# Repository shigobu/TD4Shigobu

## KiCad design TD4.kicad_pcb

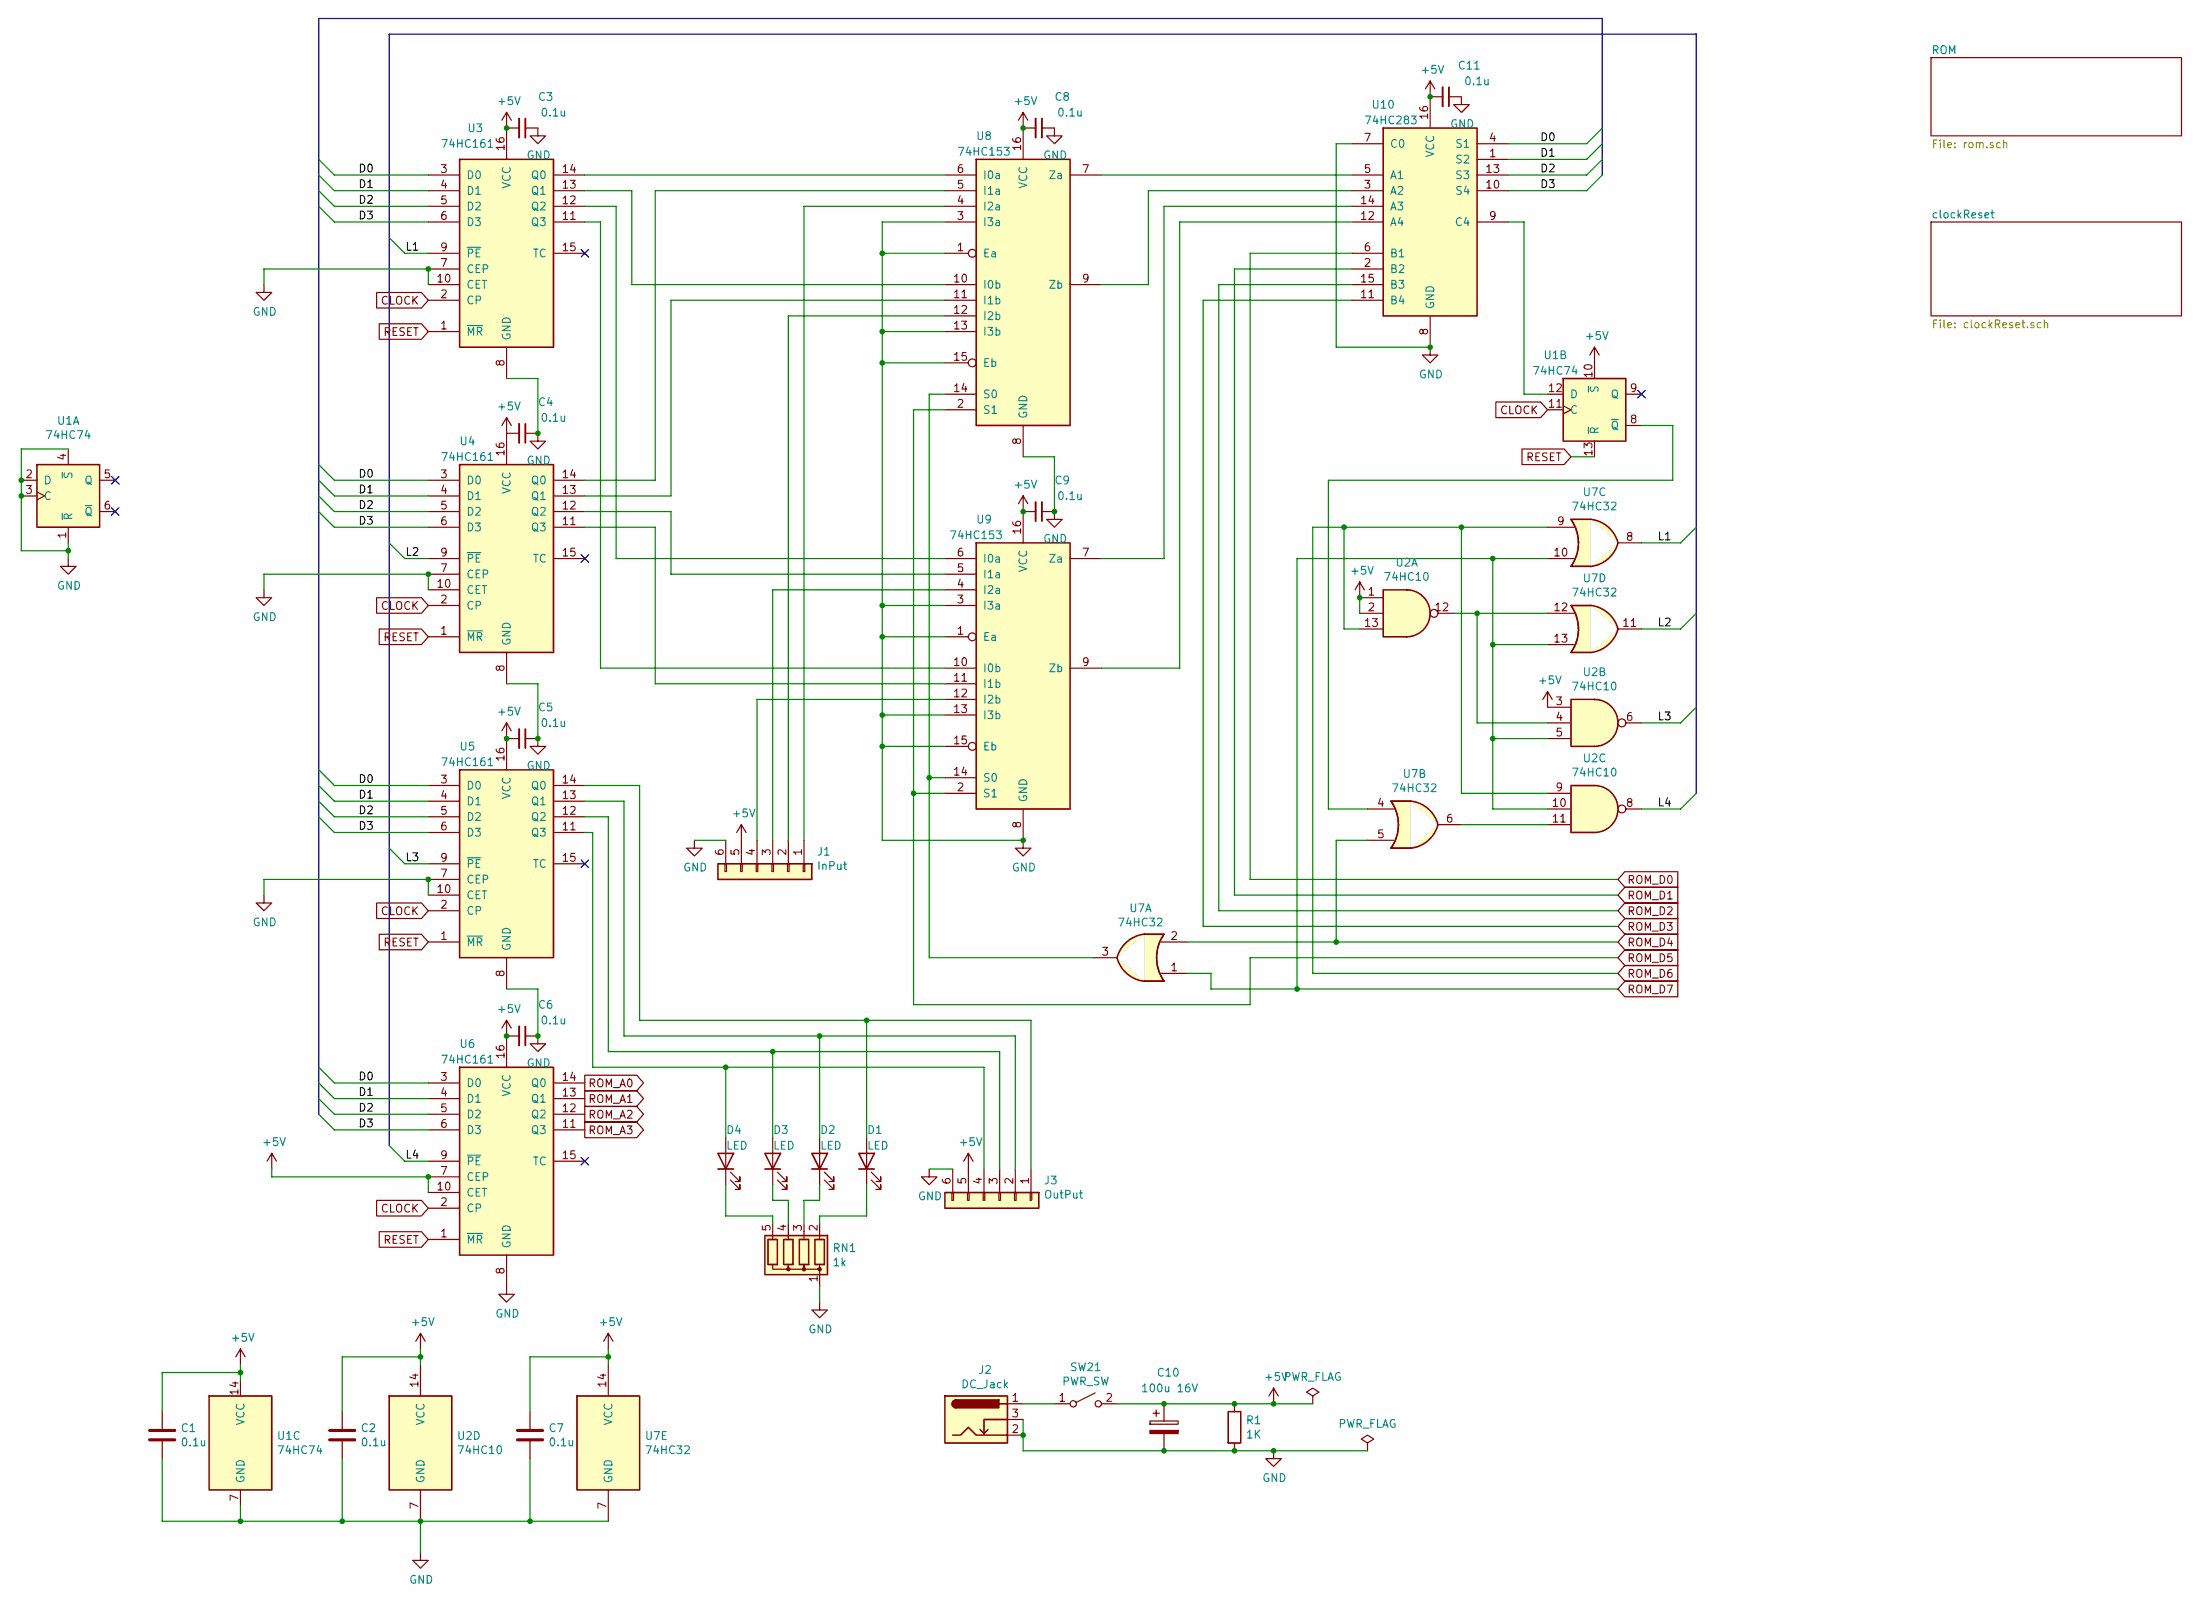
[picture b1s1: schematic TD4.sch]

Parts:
C1, C2, C3, C4, C5, C6, C7, C8, C9, C11: 0.1u; C_Disc_D3.0mm_W2.0mm_P2.50mm
C10: 100u 16V; CP_Radial_D5.0mm_P2.00mm
D1, D2, D3, D4: LED; LED_D3.0mm
J1: InPut; PinHeader_1x06_P2.54mm_Vertical
J2: DC_Jack; BarrelJack_Wuerth_6941xx301002
J3: OutPut; PinHeader_1x06_P2.54mm_Vertical
R1: 1K; R_Axial_DIN0207_L6.3mm_D2.5mm_P7.62mm_Horizontal
RN1: 1k; R_Array_SIP5
SW21: PWR_SW; SW_CuK_JS202011CQN_DPDT_Straight
U1: 74HC74; DIP-14_W7.62mm_Socket
U2: 74HC10; DIP-14_W7.62mm_Socket
U3, U4, U5, U6: 74HC161; DIP-16_W7.62mm_Socket
U7: 74HC32; DIP-14_W7.62mm_Socket
U8, U9: 74HC153; DIP-16_W7.62mm_Socket
U10: 74HC283; DIP-16_W7.62mm_Socket

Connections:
+5V: C1.1, C2.1, C3.2, C4.2, C5.2, C6.2, C7.1, C8.2, C9.2, C10.1, C11.2, J1.5, J3.5, R1.1, SW21.2 (B), U1.10 (~S), U1.14 (VCC), U2.1, U2.2, U2.3, U2.14 (VCC), U3.16 (VCC), U4.16 (VCC), U5.16 (VCC), U6.7 (CEP), U6.10 (CET), U6.16 (VCC), U7.14 (VCC), U8.16 (VCC), U9.16 (VCC), U10.16 (VCC); also elsewhere on the board
/D0: U3.3 (D0), U4.3 (D0), U5.3 (D0), U6.3 (D0), U10.4 (S1)
/D1: U3.4 (D1), U4.4 (D1), U5.4 (D1), U6.4 (D1), U10.1 (S2)
/D2: U3.5 (D2), U4.5 (D2), U5.5 (D2), U6.5 (D2), U10.13 (S3)
/D3: U3.6 (D3), U4.6 (D3), U5.6 (D3), U6.6 (D3), U10.10 (S4)
/L1: U3.9 (~PE), U7.8
/L2: U4.9 (~PE), U7.11
/L3: U2.6, U5.9 (~PE)
/L4: U2.8, U6.9 (~PE)
CLOCK: U1.11 (C), U3.2 (CP), U4.2 (CP), U5.2 (CP), U6.2 (CP); also elsewhere on the board
GND: C1.2, C2.2, C3.1, C4.1, C5.1, C6.1, C7.2, C8.1, C9.1, C10.2, C11.1, J1.6, J2.2, J2.3, J3.6, R1.2, RN1.1 (common), U1.1 (~R), U1.2 (D), U1.3 (C), U1.4 (~S), U1.7 (GND), U2.7 (GND), U3.7 (CEP), U3.8 (GND), U3.10 (CET), U4.7 (CEP), U4.8 (GND), U4.10 (CET), U5.7 (CEP), U5.8 (GND), U5.10 (CET), U6.8 (GND), U7.7 (GND), U8.1 (Ea), U8.3 (I3a), U8.8 (GND), U8.13 (I3b), U8.15 (Eb), U9.1 (Ea), U9.3 (I3a), U9.8 (GND), U9.13 (I3b), U9.15 (Eb), U10.7 (C0), U10.8 (GND); also elsewhere on the board
unnamed: D1.1 (K), RN1.2 (R1)
unnamed: D1.2 (A), J3.1, U5.14 (Q0)
unnamed: D2.1 (K), RN1.3 (R2)
unnamed: D2.2 (A), J3.2, U5.13 (Q1)
unnamed: D3.1 (K), RN1.4 (R3)
unnamed: D3.2 (A), J3.3, U5.12 (Q2)
unnamed: D4.1 (K), RN1.5 (R4)
unnamed: D4.2 (A), J3.4, U5.11 (Q3)
unnamed: J1.1, U8.4 (I2a)
unnamed: J1.2, U8.12 (I2b)
unnamed: J1.3, U9.4 (I2a)
unnamed: J1.4, U9.12 (I2b)
unnamed: J2.1, SW21.1 (A)
unnamed: U1.8 (~Q), U7.4
unnamed: U1.12 (D), U10.9 (C4)
unnamed: U2.11, U7.6
unnamed: U2.4, U2.12, U7.12
unnamed: U3.11 (Q3), U9.10 (I0b)
unnamed: U3.12 (Q2), U9.6 (I0a)
unnamed: U3.13 (Q1), U8.10 (I0b)
unnamed: U3.14 (Q0), U8.6 (I0a)
unnamed: U4.11 (Q3), U9.11 (I1b)
unnamed: U4.12 (Q2), U9.5 (I1a)
unnamed: U4.13 (Q1), U8.11 (I1b)
unnamed: U4.14 (Q0), U8.5 (I1a)
unnamed: U7.3, U8.14 (S0), U9.14 (S0)
unnamed: U8.9 (Zb), U10.3 (A2)
unnamed: U8.7 (Za), U10.5 (A1)
unnamed: U9.9 (Zb), U10.12 (A4)
unnamed: U9.7 (Za), U10.14 (A3)
RESET: U1.13 (~R), U3.1 (~MR), U4.1 (~MR), U5.1 (~MR), U6.1 (~MR); also elsewhere on the board
ROM_A0: U6.14 (Q0); also elsewhere on the board
ROM_A1: U6.13 (Q1); also elsewhere on the board
ROM_A2: U6.12 (Q2); also elsewhere on the board
ROM_A3: U6.11 (Q3); also elsewhere on the board
ROM_D0: U10.6 (B1); also elsewhere on the board
ROM_D1: U10.2 (B2); also elsewhere on the board
ROM_D2: U10.15 (B3); also elsewhere on the board
ROM_D3: U10.11 (B4); also elsewhere on the board
ROM_D4: U7.2, U7.5; also elsewhere on the board
ROM_D5: U8.2 (S1), U9.2 (S1); also elsewhere on the board
ROM_D6: U2.9, U2.13, U7.9; also elsewhere on the board
ROM_D7: U2.5, U2.10, U7.1, U7.10, U7.13; also elsewhere on the board

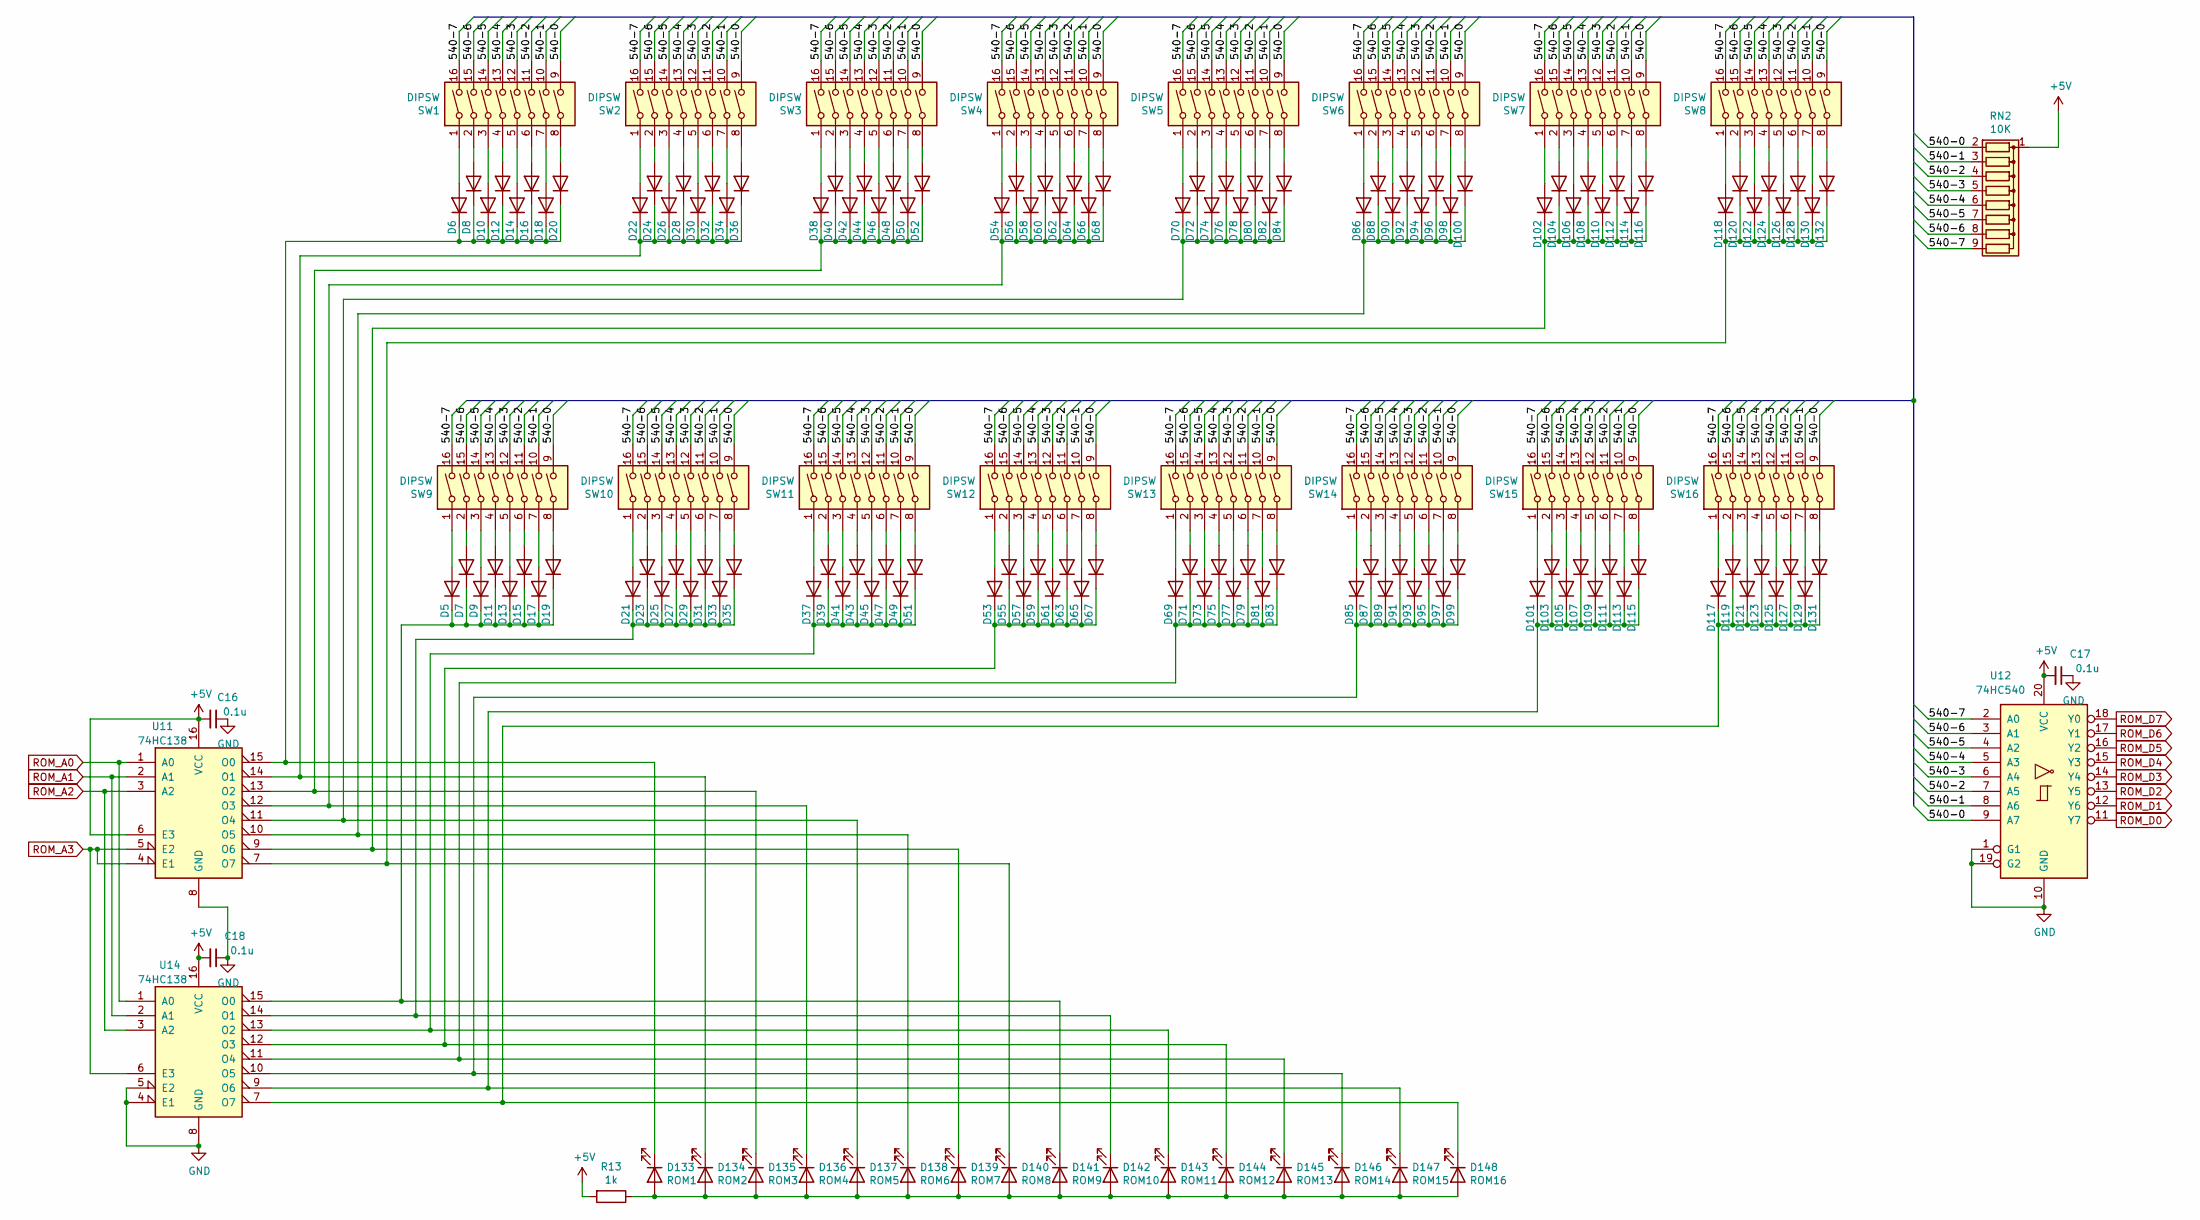
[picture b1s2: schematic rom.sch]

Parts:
C16, C17, C18: 0.1u; C_Disc_D3.0mm_W2.0mm_P2.50mm
D5, D6, D9, D10, D13, D14, D17, D18, D21, D22, D25, D26, D29, D30, D33, D34, D37, D38, D41, D42, D45, D46, D49, D50, D53, D54, D57, D58, D61, D62, D65, D66, D69, D70, D73, D74, D77, D78, D81, D82, D85, D86, D89, D90, D93, D94, D97, D98, D101, D102, D105, D106, D109, D110, D113, D114, D117, D118, D121, D122, D125, D126, D129, D130: D; D_DO-34_SOD68_P2.54mm_Vertical_AnodeUp
D7, D8, D11, D12, D15, D16, D19, D20, D23, D24, D27, D28, D31, D32, D35, D36, D39, D40, D43, D44, D47, D48, D51, D52, D55, D56, D59, D60, D63, D64, D67, D68, D71, D72, D75, D76, D79, D80, D83, D84, D87, D88, D91, D92, D95, D96, D99, D100, D103, D104, D107, D108, D111, D112, D115, D116, D119, D120, D123, D124, D127, D128, D131, D132: D; D_DO-34_SOD68_P2.54mm_Vertical_KathodeUp
D133: ROM1; LED_D3.0mm
D134: ROM2; LED_D3.0mm
D135: ROM3; LED_D3.0mm
D136: ROM4; LED_D3.0mm
D137: ROM5; LED_D3.0mm
D138: ROM6; LED_D3.0mm
D139: ROM7; LED_D3.0mm
D140: ROM8; LED_D3.0mm
D141: ROM9; LED_D3.0mm
D142: ROM10; LED_D3.0mm
D143: ROM11; LED_D3.0mm
D144: ROM12; LED_D3.0mm
D145: ROM13; LED_D3.0mm
D146: ROM14; LED_D3.0mm
D147: ROM15; LED_D3.0mm
D148: ROM16; LED_D3.0mm
R13: 1k; R_Axial_DIN0207_L6.3mm_D2.5mm_P7.62mm_Horizontal
RN2: 10K; R_Array_SIP9
SW1, SW2, SW3, SW4, SW5, SW6, SW7, SW8, SW9, SW10, SW11, SW12, SW13, SW14, SW15, SW16: DIPSW; SW_DIP_SPSTx08_Slide_9.78x22.5mm_W7.62mm_P2.54mm
U11, U14: 74HC138; DIP-16_W7.62mm_Socket
U12: 74HC540; DIP-20_W7.62mm_Socket

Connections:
+5V: C16.2, C17.2, C18.2, R13.2, RN2.1 (common), U11.6 (E3), U11.16 (VCC), U12.20 (VCC), U14.16 (VCC); also elsewhere on the board
/ROM/540-0: RN2.2 (R1), SW1.9, SW2.9, SW3.9, SW4.9, SW5.9, SW6.9, SW7.9, SW8.9, SW9.9, SW10.9, SW11.9, SW12.9, SW13.9, SW14.9, SW15.9, SW16.9, U12.9 (A7)
/ROM/540-1: RN2.3 (R2), SW1.10, SW2.10, SW3.10, SW4.10, SW5.10, SW6.10, SW7.10, SW8.10, SW9.10, SW10.10, SW11.10, SW12.10, SW13.10, SW14.10, SW15.10, SW16.10, U12.8 (A6)
/ROM/540-2: RN2.4 (R3), SW1.11, SW2.11, SW3.11, SW4.11, SW5.11, SW6.11, SW7.11, SW8.11, SW9.11, SW10.11, SW11.11, SW12.11, SW13.11, SW14.11, SW15.11, SW16.11, U12.7 (A5)
/ROM/540-3: RN2.5 (R4), SW1.12, SW2.12, SW3.12, SW4.12, SW5.12, SW6.12, SW7.12, SW8.12, SW9.12, SW10.12, SW11.12, SW12.12, SW13.12, SW14.12, SW15.12, SW16.12, U12.6 (A4)
/ROM/540-4: RN2.6 (R5), SW1.13, SW2.13, SW3.13, SW4.13, SW5.13, SW6.13, SW7.13, SW8.13, SW9.13, SW10.13, SW11.13, SW12.13, SW13.13, SW14.13, SW15.13, SW16.13, U12.5 (A3)
/ROM/540-5: RN2.7 (R6), SW1.14, SW2.14, SW3.14, SW4.14, SW5.14, SW6.14, SW7.14, SW8.14, SW9.14, SW10.14, SW11.14, SW12.14, SW13.14, SW14.14, SW15.14, SW16.14, U12.4 (A2)
/ROM/540-6: RN2.8 (R7), SW1.15, SW2.15, SW3.15, SW4.15, SW5.15, SW6.15, SW7.15, SW8.15, SW9.15, SW10.15, SW11.15, SW12.15, SW13.15, SW14.15, SW15.15, SW16.15, U12.3 (A1)
/ROM/540-7: RN2.9 (R8), SW1.16, SW2.16, SW3.16, SW4.16, SW5.16, SW6.16, SW7.16, SW8.16, SW9.16, SW10.16, SW11.16, SW12.16, SW13.16, SW14.16, SW15.16, SW16.16, U12.2 (A0)
GND: C16.1, C17.1, C18.1, U11.8 (GND), U12.1 (G1), U12.10 (GND), U12.19 (G2), U14.4 (E1), U14.5 (E2), U14.8 (GND); also elsewhere on the board
unnamed: D5.2 (A), SW9.1
unnamed: D6.2 (A), SW1.1
unnamed: D7.2 (A), SW9.2
unnamed: D8.2 (A), SW1.2
unnamed: D9.2 (A), SW9.3
unnamed: D6.1 (K), D8.1 (K), D10.1 (K), D12.1 (K), D14.1 (K), D16.1 (K), D18.1 (K), D20.1 (K), D133.1 (K), U11.15 (O0)
unnamed: D10.2 (A), SW1.3
unnamed: D5.1 (K), D7.1 (K), D9.1 (K), D11.1 (K), D13.1 (K), D15.1 (K), D17.1 (K), D19.1 (K), D141.1 (K), U14.15 (O0)
unnamed: D11.2 (A), SW9.4
unnamed: D12.2 (A), SW1.4
unnamed: D13.2 (A), SW9.5
unnamed: D14.2 (A), SW1.5
unnamed: D15.2 (A), SW9.6
unnamed: D16.2 (A), SW1.6
unnamed: D17.2 (A), SW9.7
unnamed: D18.2 (A), SW1.7
unnamed: D19.2 (A), SW9.8
unnamed: D20.2 (A), SW1.8
unnamed: D21.2 (A), SW10.1
unnamed: D22.2 (A), SW2.1
unnamed: D23.2 (A), SW10.2
unnamed: D24.2 (A), SW2.2
unnamed: D25.2 (A), SW10.3
unnamed: D26.2 (A), SW2.3
unnamed: D27.2 (A), SW10.4
unnamed: D28.2 (A), SW2.4
unnamed: D29.2 (A), SW10.5
unnamed: D30.2 (A), SW2.5
unnamed: D31.2 (A), SW10.6
unnamed: D32.2 (A), SW2.6
unnamed: D33.2 (A), SW10.7
unnamed: D34.2 (A), SW2.7
unnamed: D35.2 (A), SW10.8
unnamed: D36.2 (A), SW2.8
unnamed: D37.2 (A), SW11.1
unnamed: D38.2 (A), SW3.1
unnamed: D39.2 (A), SW11.2
unnamed: D40.2 (A), SW3.2
unnamed: D41.2 (A), SW11.3
unnamed: D42.2 (A), SW3.3
unnamed: D43.2 (A), SW11.4
unnamed: D44.2 (A), SW3.4
unnamed: D45.2 (A), SW11.5
unnamed: D46.2 (A), SW3.5
unnamed: D47.2 (A), SW11.6
unnamed: D48.2 (A), SW3.6
unnamed: D49.2 (A), SW11.7
unnamed: D50.2 (A), SW3.7
unnamed: D51.2 (A), SW11.8
unnamed: D52.2 (A), SW3.8
unnamed: D53.2 (A), SW12.1
unnamed: D54.2 (A), SW4.1
unnamed: D55.2 (A), SW12.2
unnamed: D56.2 (A), SW4.2
unnamed: D57.2 (A), SW12.3
unnamed: D58.2 (A), SW4.3
unnamed: D59.2 (A), SW12.4
unnamed: D60.2 (A), SW4.4
unnamed: D61.2 (A), SW12.5
unnamed: D62.2 (A), SW4.5
unnamed: D63.2 (A), SW12.6
unnamed: D64.2 (A), SW4.6
unnamed: D65.2 (A), SW12.7
unnamed: D66.2 (A), SW4.7
unnamed: D67.2 (A), SW12.8
unnamed: D68.2 (A), SW4.8
unnamed: D69.2 (A), SW13.1
unnamed: D70.2 (A), SW5.1
unnamed: D71.2 (A), SW13.2
unnamed: D72.2 (A), SW5.2
unnamed: D73.2 (A), SW13.3
unnamed: D74.2 (A), SW5.3
unnamed: D75.2 (A), SW13.4
unnamed: D76.2 (A), SW5.4
unnamed: D77.2 (A), SW13.5
unnamed: D78.2 (A), SW5.5
unnamed: D79.2 (A), SW13.6
unnamed: D80.2 (A), SW5.6
unnamed: D81.2 (A), SW13.7
unnamed: D82.2 (A), SW5.7
unnamed: D83.2 (A), SW13.8
unnamed: D84.2 (A), SW5.8
unnamed: D85.2 (A), SW14.1
unnamed: D86.2 (A), SW6.1
unnamed: D87.2 (A), SW14.2
unnamed: D88.2 (A), SW6.2
unnamed: D89.2 (A), SW14.3
unnamed: D90.2 (A), SW6.3
unnamed: D91.2 (A), SW14.4
unnamed: D92.2 (A), SW6.4
unnamed: D93.2 (A), SW14.5
unnamed: D94.2 (A), SW6.5
unnamed: D95.2 (A), SW14.6
unnamed: D96.2 (A), SW6.6
unnamed: D97.2 (A), SW14.7
unnamed: D98.2 (A), SW6.7
unnamed: D99.2 (A), SW14.8
unnamed: D86.1 (K), D88.1 (K), D90.1 (K), D92.1 (K), D94.1 (K), D96.1 (K), D98.1 (K), D100.1 (K), D138.1 (K), U11.10 (O5)
unnamed: D100.2 (A), SW6.8
unnamed: D101.1 (K), D103.1 (K), D105.1 (K), D107.1 (K), D109.1 (K), D111.1 (K), D113.1 (K), D115.1 (K), D147.1 (K), U14.9 (O6)
unnamed: D101.2 (A), SW15.1
unnamed: D102.1 (K), D104.1 (K), D106.1 (K), D108.1 (K), D110.1 (K), D112.1 (K), D114.1 (K), D116.1 (K), D139.1 (K), U11.9 (O6)
unnamed: D102.2 (A), SW7.1
unnamed: D103.2 (A), SW15.2
unnamed: D104.2 (A), SW7.2
unnamed: D105.2 (A), SW15.3
unnamed: D106.2 (A), SW7.3
unnamed: D107.2 (A), SW15.4
unnamed: D108.2 (A), SW7.4
unnamed: D109.2 (A), SW15.5
unnamed: D110.2 (A), SW7.5
unnamed: D111.2 (A), SW15.6
unnamed: D112.2 (A), SW7.6
unnamed: D113.2 (A), SW15.7
unnamed: D114.2 (A), SW7.7
unnamed: D115.2 (A), SW15.8
unnamed: D116.2 (A), SW7.8
unnamed: D117.1 (K), D119.1 (K), D121.1 (K), D123.1 (K), D125.1 (K), D127.1 (K), D129.1 (K), D131.1 (K), D148.1 (K), U14.7 (O7)
unnamed: D117.2 (A), SW16.1
unnamed: D118.1 (K), D120.1 (K), D122.1 (K), D124.1 (K), D126.1 (K), D128.1 (K), D130.1 (K), D132.1 (K), D140.1 (K), U11.7 (O7)
unnamed: D118.2 (A), SW8.1
unnamed: D119.2 (A), SW16.2
unnamed: D120.2 (A), SW8.2
unnamed: D121.2 (A), SW16.3
unnamed: D122.2 (A), SW8.3
unnamed: D123.2 (A), SW16.4
unnamed: D124.2 (A), SW8.4
unnamed: D125.2 (A), SW16.5
unnamed: D126.2 (A), SW8.5
unnamed: D127.2 (A), SW16.6
unnamed: D128.2 (A), SW8.6
unnamed: D129.2 (A), SW16.7
unnamed: D130.2 (A), SW8.7
unnamed: D131.2 (A), SW16.8
unnamed: D132.2 (A), SW8.8
unnamed: D133.2 (A), D134.2 (A), D135.2 (A), D136.2 (A), D137.2 (A), D138.2 (A), D139.2 (A), D140.2 (A), D141.2 (A), D142.2 (A), D143.2 (A), D144.2 (A), D145.2 (A), D146.2 (A), D147.2 (A), D148.2 (A), R13.1
unnamed: D22.1 (K), D24.1 (K), D26.1 (K), D28.1 (K), D30.1 (K), D32.1 (K), D34.1 (K), D36.1 (K), D134.1 (K), U11.14 (O1)
unnamed: D38.1 (K), D40.1 (K), D42.1 (K), D44.1 (K), D46.1 (K), D48.1 (K), D50.1 (K), D52.1 (K), D135.1 (K), U11.13 (O2)
unnamed: D54.1 (K), D56.1 (K), D58.1 (K), D60.1 (K), D62.1 (K), D64.1 (K), D66.1 (K), D68.1 (K), D136.1 (K), U11.12 (O3)
unnamed: D70.1 (K), D72.1 (K), D74.1 (K), D76.1 (K), D78.1 (K), D80.1 (K), D82.1 (K), D84.1 (K), D137.1 (K), U11.11 (O4)
unnamed: D21.1 (K), D23.1 (K), D25.1 (K), D27.1 (K), D29.1 (K), D31.1 (K), D33.1 (K), D35.1 (K), D142.1 (K), U14.14 (O1)
unnamed: D37.1 (K), D39.1 (K), D41.1 (K), D43.1 (K), D45.1 (K), D47.1 (K), D49.1 (K), D51.1 (K), D143.1 (K), U14.13 (O2)
unnamed: D53.1 (K), D55.1 (K), D57.1 (K), D59.1 (K), D61.1 (K), D63.1 (K), D65.1 (K), D67.1 (K), D144.1 (K), U14.12 (O3)
unnamed: D69.1 (K), D71.1 (K), D73.1 (K), D75.1 (K), D77.1 (K), D79.1 (K), D81.1 (K), D83.1 (K), D145.1 (K), U14.11 (O4)
unnamed: D85.1 (K), D87.1 (K), D89.1 (K), D91.1 (K), D93.1 (K), D95.1 (K), D97.1 (K), D99.1 (K), D146.1 (K), U14.10 (O5)
ROM_A0: U11.1 (A0), U14.1 (A0); also elsewhere on the board
ROM_A1: U11.2 (A1), U14.2 (A1); also elsewhere on the board
ROM_A2: U11.3 (A2), U14.3 (A2); also elsewhere on the board
ROM_A3: U11.4 (E1), U11.5 (E2), U14.6 (E3); also elsewhere on the board
ROM_D0: U12.11 (Y7); also elsewhere on the board
ROM_D1: U12.12 (Y6); also elsewhere on the board
ROM_D2: U12.13 (Y5); also elsewhere on the board
ROM_D3: U12.14 (Y4); also elsewhere on the board
ROM_D4: U12.15 (Y3); also elsewhere on the board
ROM_D5: U12.16 (Y2); also elsewhere on the board
ROM_D6: U12.17 (Y1); also elsewhere on the board
ROM_D7: U12.18 (Y0); also elsewhere on the board

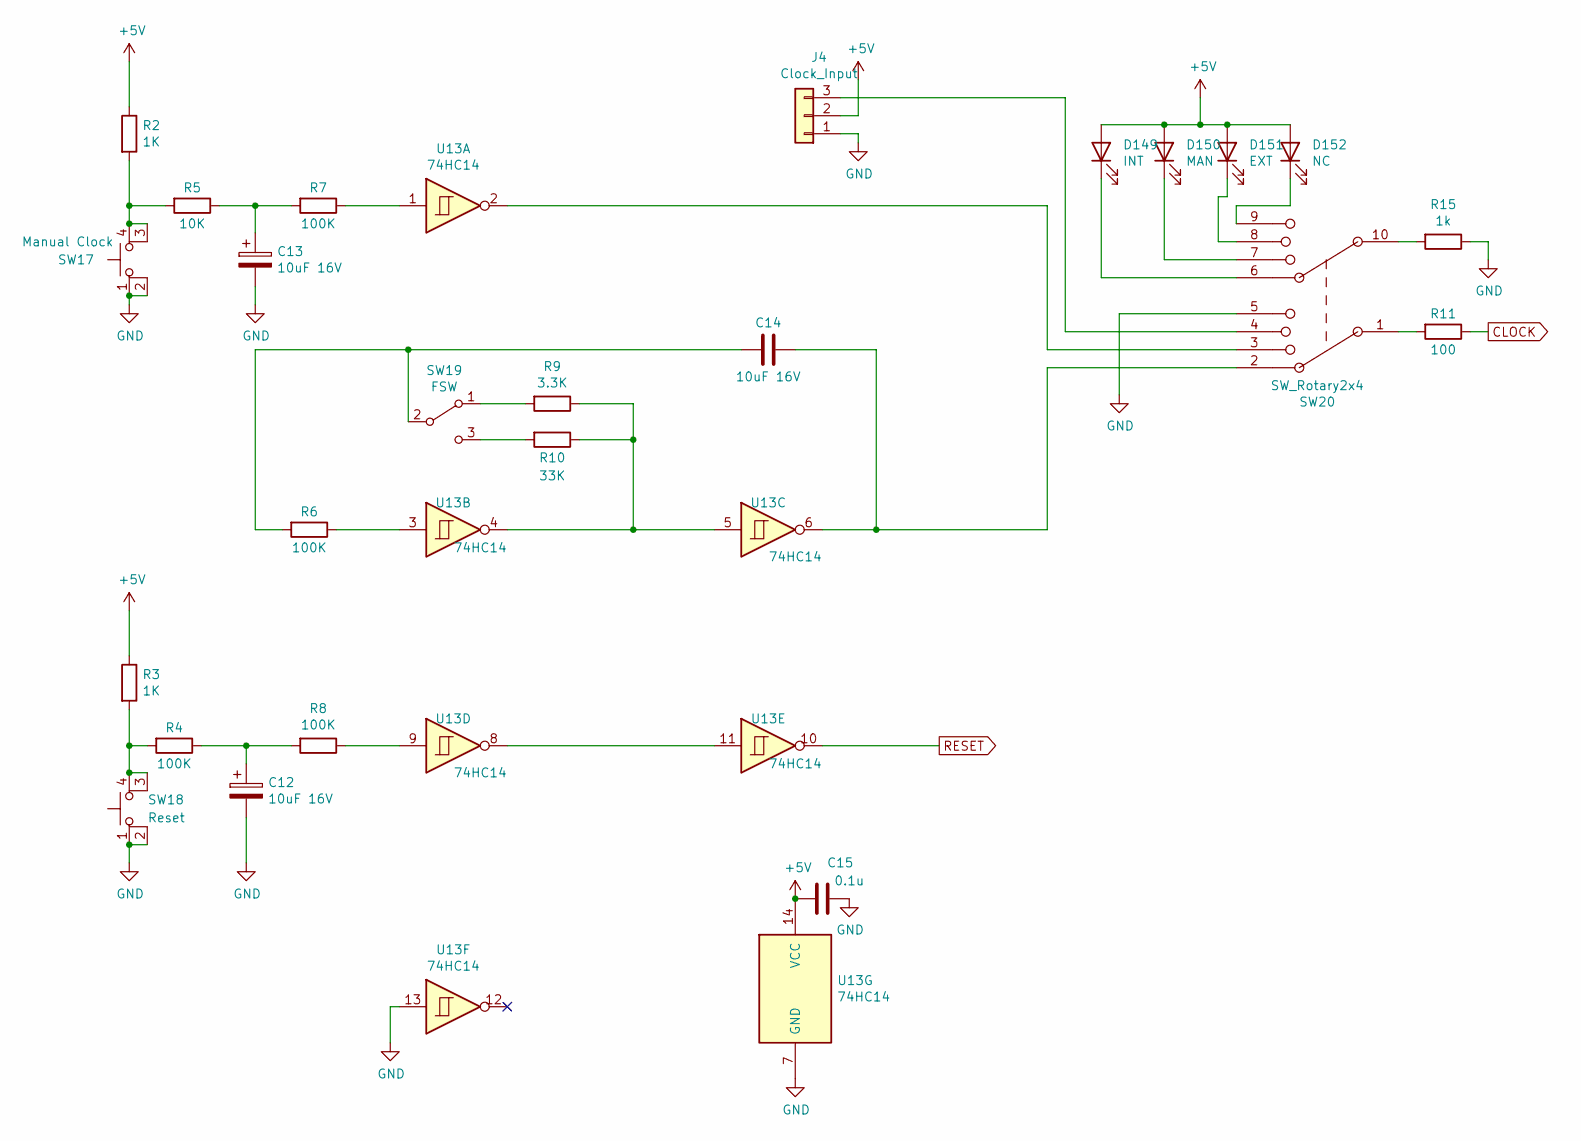
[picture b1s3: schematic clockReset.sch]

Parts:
C12, C13, C14: 10uF 16V; C_Disc_D5.1mm_W3.2mm_P5.00mm
C15: 0.1u; C_Disc_D3.0mm_W2.0mm_P2.50mm
D149: INT; LED_D3.0mm
D150: MAN; LED_D3.0mm
D151: EXT; LED_D3.0mm
D152: NC; LED_D3.0mm
J4: Clock_Input; PinHeader_1x03_P2.54mm_Vertical
R2, R3: 1K; R_Axial_DIN0207_L6.3mm_D2.5mm_P7.62mm_Horizontal
R4, R6, R7, R8: 100K; R_Axial_DIN0207_L6.3mm_D2.5mm_P7.62mm_Horizontal
R5: 10K; R_Axial_DIN0207_L6.3mm_D2.5mm_P7.62mm_Horizontal
R9: 3.3K; R_Axial_DIN0207_L6.3mm_D2.5mm_P7.62mm_Horizontal
R10: 33K; R_Axial_DIN0207_L6.3mm_D2.5mm_P7.62mm_Horizontal
R11: 100; R_Axial_DIN0207_L6.3mm_D2.5mm_P7.62mm_Horizontal
R15: 1k; R_Axial_DIN0207_L6.3mm_D2.5mm_P7.62mm_Horizontal
SW17: Manual Clock; SW_TH_Tactile_Omron_B3F-10xx
SW18: Reset; SW_TH_Tactile_Omron_B3F-10xx
SW19: FSW; SW_CuK_JS202011CQN_DPDT_Straight
SW20: SW_Rotary2x4; Rotary_Switch 10pin
U13: 74HC14; DIP-14_W7.62mm_Socket

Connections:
+5V: C15.2, D149.2 (A), D150.2 (A), D151.2 (A), D152.2 (A), J4.2, R2.1, R3.1, U13.14 (VCC); also elsewhere on the board
CLOCK: R11.1; also elsewhere on the board
GND: C12.2, C13.2, C15.1, J4.1, R15.1, SW17.1, SW17.2, SW18.1, SW18.2, SW20.5, SW20.11, U13.7 (GND), U13.13; also elsewhere on the board
unnamed: C12.1, R4.1, R8.2
unnamed: C13.1, R5.1, R7.2
unnamed: C14.1, SW20.2, U13.6
unnamed: C14.2, R6.2, SW19.2 (B)
unnamed: D149.1 (K), SW20.6
unnamed: D150.1 (K), SW20.7
unnamed: D151.1 (K), SW20.8
unnamed: D152.1 (K), SW20.9
unnamed: J4.3, SW20.4
unnamed: R2.2, R5.2, SW17.3 (K), SW17.4 (A)
unnamed: R3.2, R4.2, SW18.3 (K), SW18.4 (A)
unnamed: R6.1, U13.3
unnamed: R7.1, U13.1
unnamed: R8.1, U13.9
unnamed: R9.2, SW19.1 (A)
unnamed: R9.1, R10.1, U13.4, U13.5
unnamed: R10.2, SW19.3 (C)
unnamed: R11.2, SW20.1
unnamed: R15.2, SW20.10
unnamed: SW20.3, U13.2
unnamed: U13.8, U13.11
RESET: U13.10; also elsewhere on the board

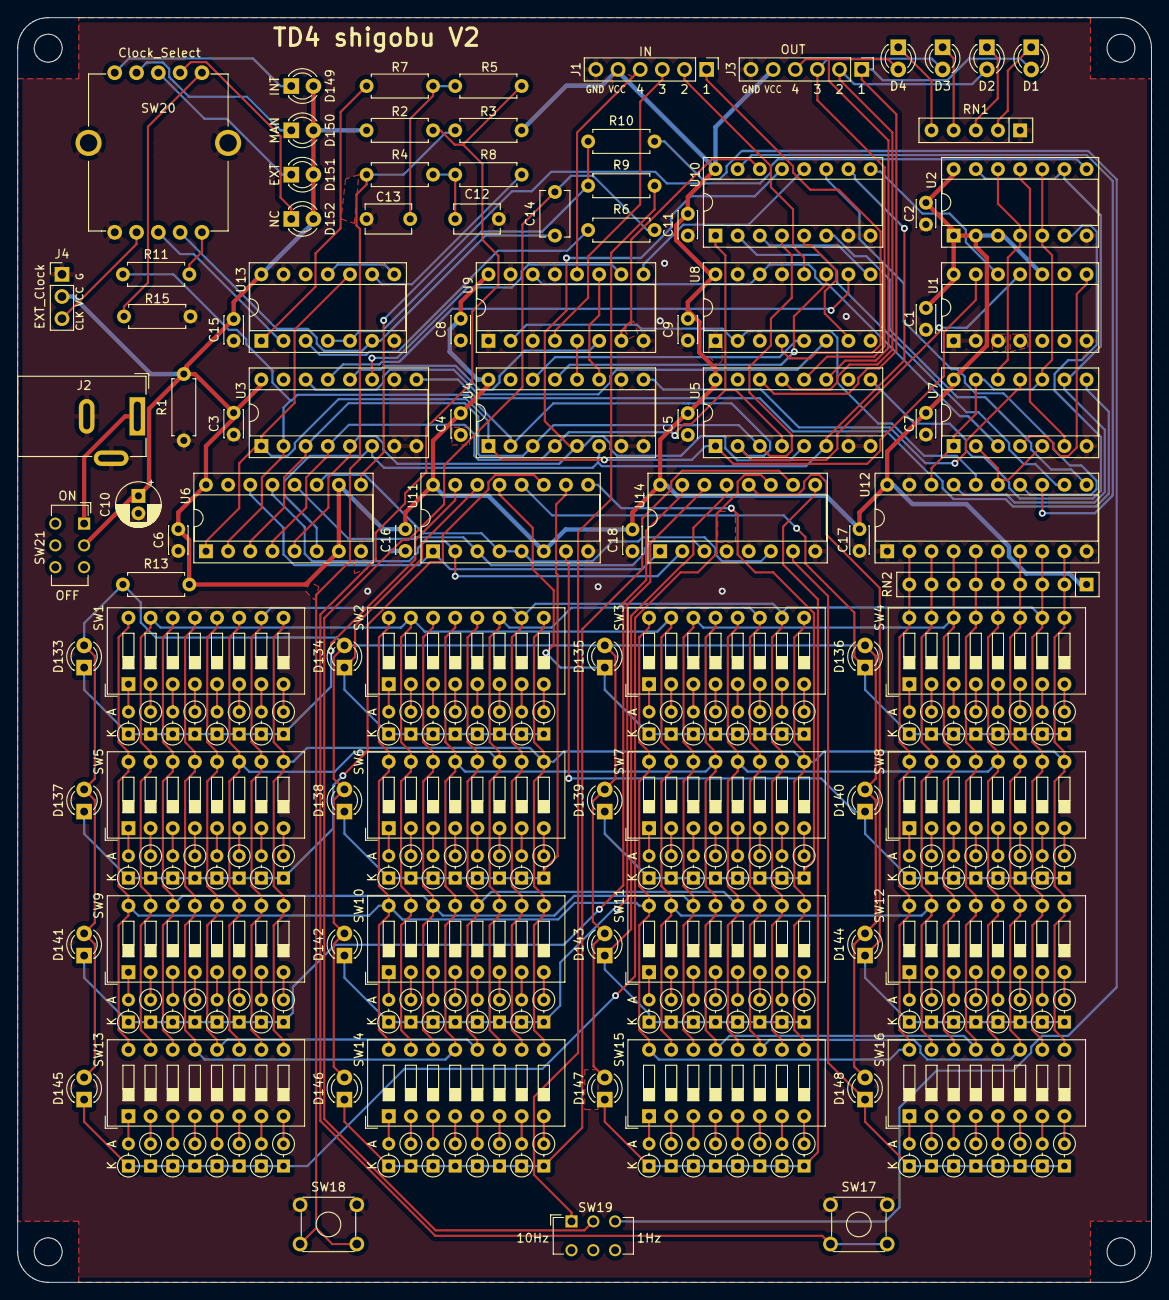
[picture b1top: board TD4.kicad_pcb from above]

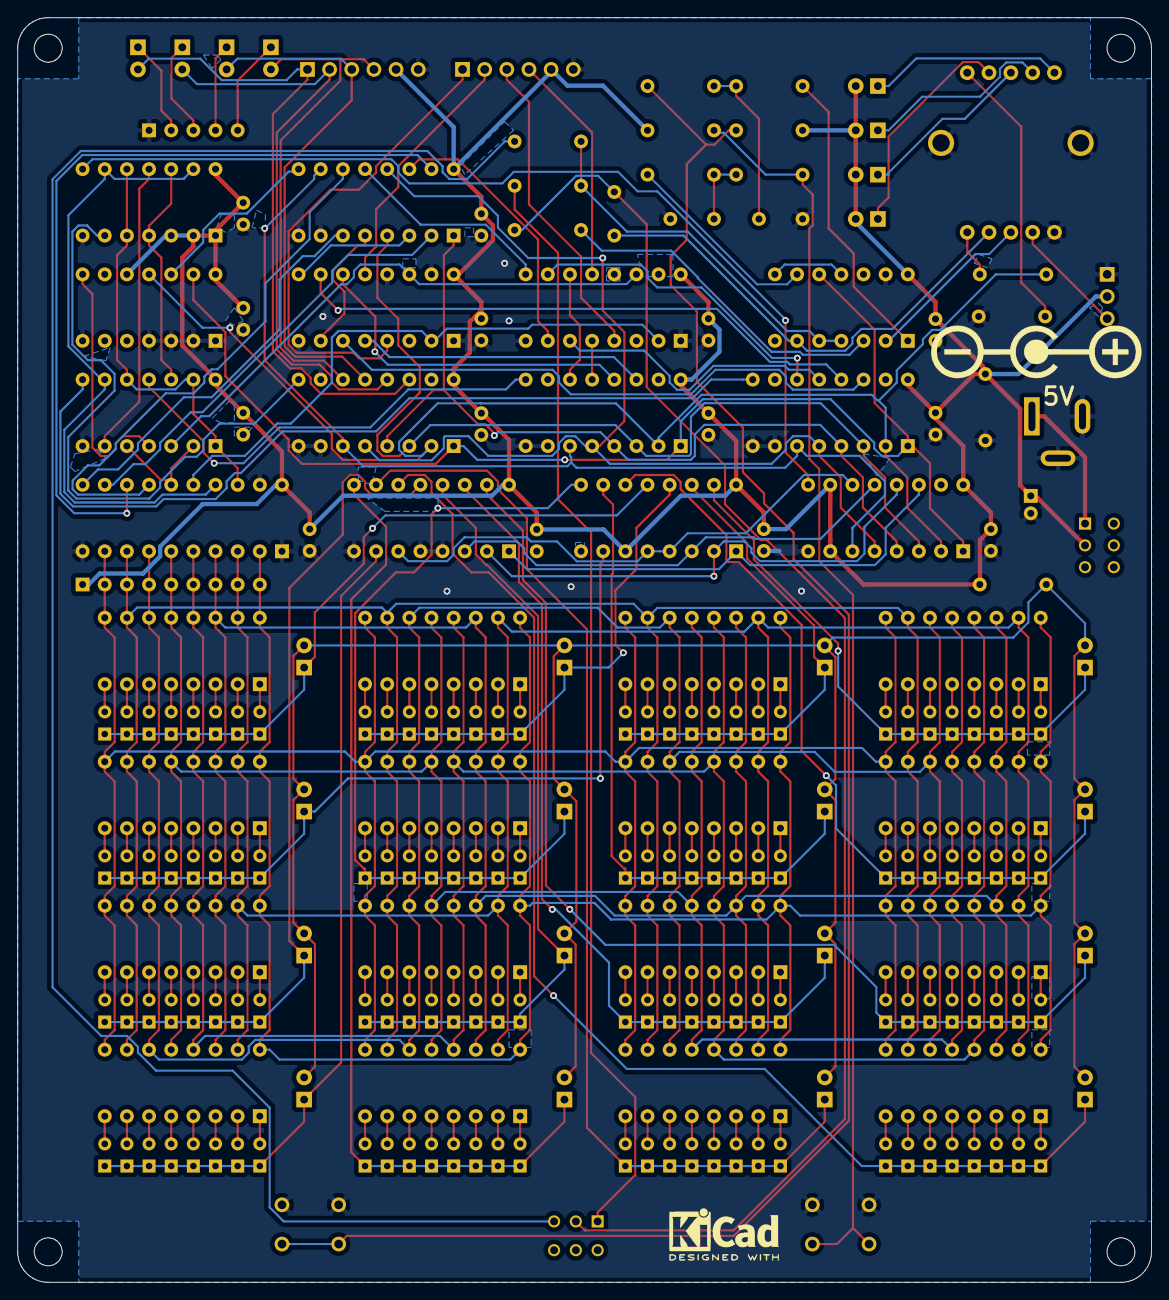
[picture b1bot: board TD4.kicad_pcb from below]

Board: 2 copper layers, 130.0 x 145.0 mm, 230 parts (2 on the bottom side), 228 nets.

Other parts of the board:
mh1, mh2, mh3, mh4: MountingHole_3.2mm_M3
sym1: KiCad-Logo2_5mm_SilkScreen
sym2: Polarity_Center_Positive_6mm_SilkScreen

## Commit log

2021-05-15 V1かんせい
2021-05-22 修正コミット
2021-05-23 配線やり直し
2021-05-23 基盤寸法追加
2022-08-08 各図面にタイトル追加
